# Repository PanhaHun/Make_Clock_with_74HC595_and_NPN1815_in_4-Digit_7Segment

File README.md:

// Define Connections 7_Segment to 74HC595
// Define Connections Digit to NPNC1815

/* 
  Showing number 0-9 on a Common Anode 7-segment LED display 
  Displays the numbers 0-9 on the display, with one second in between. 
    A 
   --- 
F |   | B 
  | G | 
   --- 
E |   | C 
  |   | 
   --- 
    D 
  This example code is in the public domain. 
  
  Q1  -  A 
  Q2  -  B 
  Q3  -  C 
  Q4  -  C 
  Q5  -  D 
  Q6  -  E 
  Q7  -  G 
  05 -  D1 
  06 -  D2 
  07 -  D3 
  08 -  D4 
 */  
 
// Patterns for characters 0,1,2,3,4,5,6,7,8,9
int Segment[10] = { B01111110,  //0 
                    B00110000,  //1
                    B01101101,  //2
                    B01111001,  //3
                    B00110011,  //4
                    B01011011,  //5
                    B01011111,  //6
                    B01110000,  //7
                    B01111111,  //8
                    B01111011,  //9
                    };
                     
// Using Real_Time_Clock DS1302
#include <virtuabotixRTC.h>

// Creation of the Real Time Clock Object
virtuabotixRTC myRTC(6, 7, 8);

// Setup Digit of 7_Segment
#define D1 2
#define D2 3
#define D3 4
#define D4 5

// ST_CP pin 12
const int latchPin = 10;
// SH_CP pin 11
const int clockPin = 11;
// DS pin 14
const int dataPin = 12;
                     
int digit1, digit2, digit3, digit4;
void setup ()
{
  // Set the current date, and time in the following format:
  // seconds, minutes, hours, day of the week, day of the month, month, year
  //                 (ss, mn, hh, 1week, DD, MM, YY);
  //    myRTC.setDS1302Time(00, 33, 21, 7, 12, 3, 2022);
  
  // Setup pins as Outputs
  pinMode(latchPin, OUTPUT);
  pinMode(clockPin, OUTPUT);
  pinMode(dataPin, OUTPUT);

  // Setup pins Digit of 7_Segment as Outputs
  for(int i=2; i<6; i++){
    pinMode(i,OUTPUT);
  }

  // Open Serial for using data
  Serial.begin(115200);

}
void loop()
{
   
  // This allows for the update of variables for time or accessing the individual elements.
  myRTC.updateTime();

  Set_time(myRTC.hours,myRTC.minutes);
//  Set_hour(myRTC.hours);
//  Set_minute(myRTC.minutes);
  
  // Start printing elements as individuals
  Serial.print("Current Date / Time: ");
  Serial.print(myRTC.dayofmonth);
  Serial.print("/");
  Serial.print(myRTC.month);
  Serial.print("/");
  Serial.print(myRTC.year);
  Serial.print("  ");
  Serial.print(myRTC.hours);
  Serial.print(":");
  Serial.print(myRTC.minutes);
  Serial.print(":");
  Serial.println(myRTC.seconds);

}

void Set_time(int h,int m){

      digit2 = h / 10;  
      digit1 = h % 10; 

      Set_num(digit2);
      digitalWrite(D1, HIGH);  
      digitalWrite(D2, LOW);
      digitalWrite(D3, LOW);  
      digitalWrite(D4, LOW); 
      delay(1);
      Set_num(digit1);
      digitalWrite(D1, LOW);  
      digitalWrite(D2, HIGH);
      digitalWrite(D3, LOW);  
      digitalWrite(D4, LOW);  
      delay(1);
      
      digit4 = m / 10;  
      digit3 = m % 10;

      Set_num(digit4);  
      digitalWrite(D1, LOW);  
      digitalWrite(D2, LOW);
      digitalWrite(D3, HIGH);  
      digitalWrite(D4, LOW);
      delay(1); 
      
      Set_num(digit3);    
      digitalWrite(D1, LOW);  
      digitalWrite(D2, LOW);
      digitalWrite(D3, LOW);  
      digitalWrite(D4, HIGH);
      delay(1); 
     
}

void  Set_num(int num){
  
      // ST_CP LOW to keep LEDs from changing while reading serial data
      digitalWrite(latchPin, LOW);
      
      shiftOut(dataPin, clockPin, LSBFIRST, Segment[num]); 
      
      // ST_CP HIGH change LEDs
      digitalWrite(latchPin, HIGH);
}

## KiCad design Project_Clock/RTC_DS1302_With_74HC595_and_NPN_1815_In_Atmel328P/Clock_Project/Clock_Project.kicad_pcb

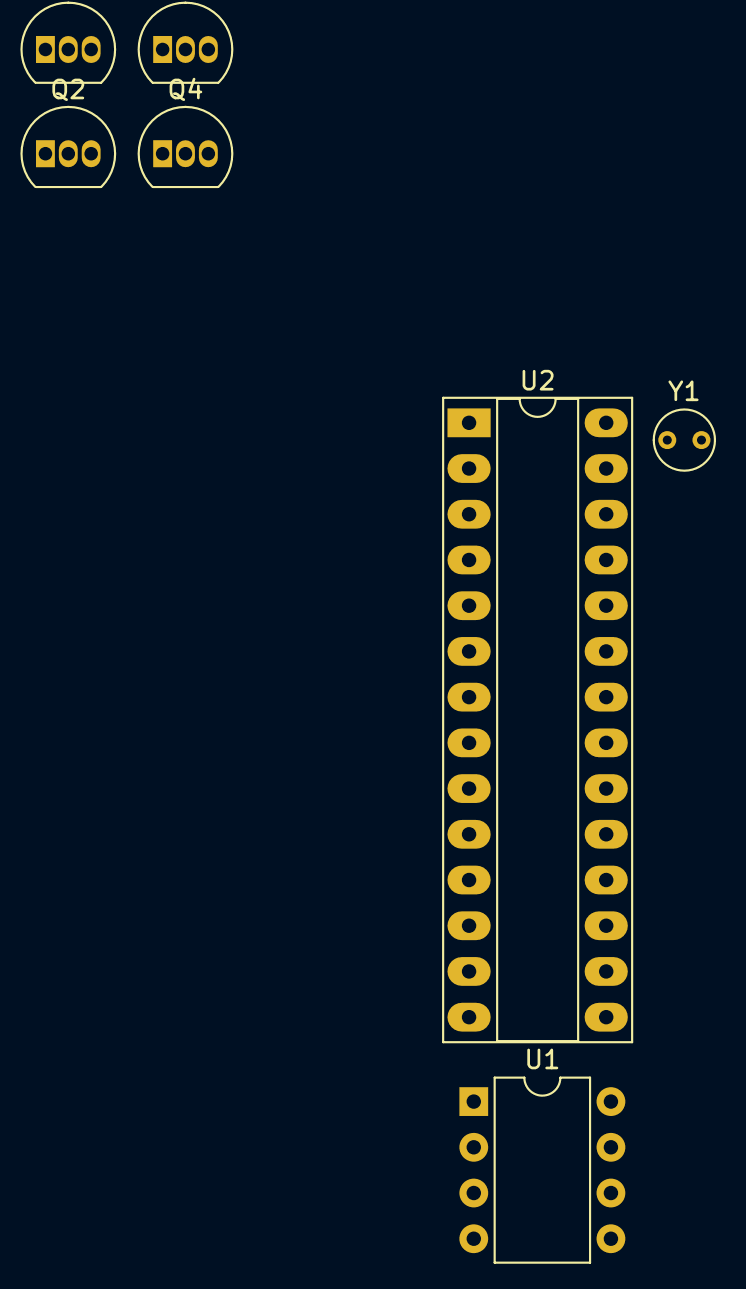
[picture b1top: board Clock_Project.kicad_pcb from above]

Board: 2 copper layers, 7 parts (0 on the bottom side), 4 nets, no tracks yet.

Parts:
Q1, Q2, Q3, Q4: 2SC1815; TO-92_Inline
U1: DS1302N+; DIP-8_W7.62mm
U2: ATmega328P-PU; DIP-28_W7.62mm_Socket_LongPads
Y1: Crystal_Small; Crystal_Round_D3.0mm_Vertical

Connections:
unnamed: Q1.1, Q2.2
unnamed: U1.2, Y1.1
unnamed: U1.3, Y1.2
unnamed: U2.8, U2.22

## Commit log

2022-03-14 Create Clock
2022-03-14 Create review
